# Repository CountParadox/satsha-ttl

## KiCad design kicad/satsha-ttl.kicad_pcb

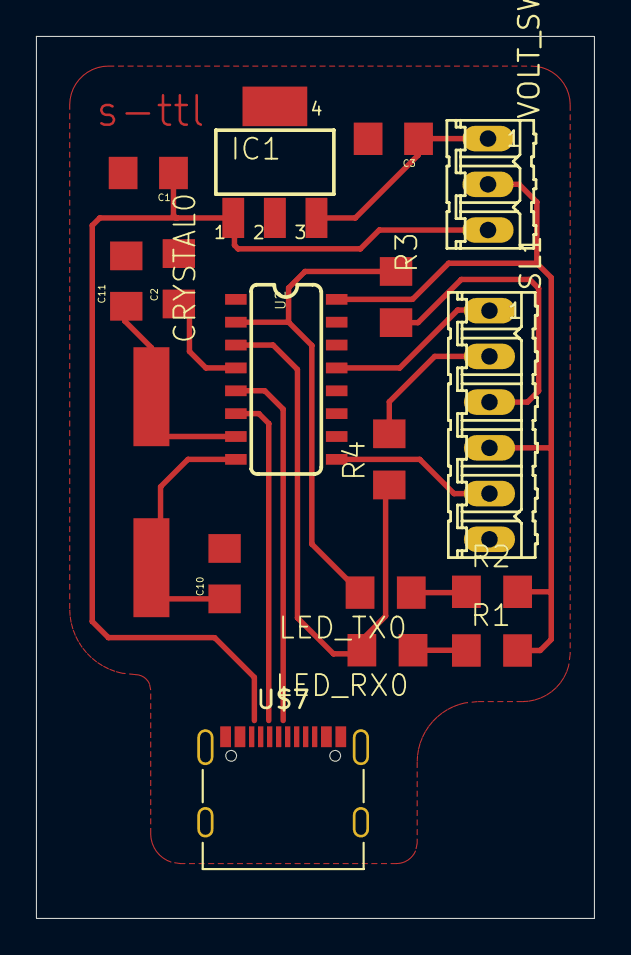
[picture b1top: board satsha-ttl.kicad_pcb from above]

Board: 2 copper layers, 31.0 x 49.0 mm, 17 parts (0 on the bottom side), 15 nets.

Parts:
C1, C3: 10uF; 1206
C2: 10nF; 1206
C10, C11: 18pF; 1206
CRYSTAL0: 12MHZ; CSM-7X-DU
IC1: MCP1703DB; SOT223
LED_RX0: YELLOW; LED1206
LED_TX0: YELLOW; LED1206
R1, R2: 2K7; R1206
R3, R4: 1K; R1206
SL1: 06P
U2: CH340G; SO016
U$7: USB-MINIB-5PIN; USB_C_Receptacle_Palconn_UTC16-G
VOLT_SWITCH0: 03P

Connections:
3V3: C3.1, IC1.3, VOLT_SWITCH0.1
5V: C1.1, IC1.1, VOLT_SWITCH0.3
CTS: SL1.5, U2.9
DTR: SL1.1, U2.13
GND: C1.2, C2.2, C3.2, C10.2, C11.2, IC1.2, SL1.6, U2.1
unnamed: LED_RX0.1, R1.1
unnamed: LED_TX0.1, R2.1
OSC_IN: C10.1, CRYSTAL0.2, U2.8
OSC_OUT: C11.1, CRYSTAL0.1, U2.7
RX: R4.2, SL1.2
RXD: LED_RX0.2, R4.1, U2.3
TX: R3.2, SL1.3
TXD: LED_TX0.2, R3.1, U2.2
V3: C2.1, U2.4
VCC: R1.2, R2.2, SL1.4, U2.16, VOLT_SWITCH0.2

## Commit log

2022-07-25 start modification for type-c 2.0 replace type-b mini and convert eagle to kicad
